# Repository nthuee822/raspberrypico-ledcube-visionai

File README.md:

# raspberrypico-ledcube-visionai
An application of a Raspberry Pi Pico–based 8x8x8 LED cube with Grove Vision AI v2 module

## Introduction

There are many tutorials online about how to build an 8x8x8 LED Cube, but very few showcase practical applications. During an exhibition, we came across the Grove Vision AI V2 module, which inspired us to combine the two into a unique project.

Here’s how our system works: the camera on the Grove Vision AI V2 first recognizes a hand gesture (rock, paper, or scissors). It then sends the result via I²C to the Raspberry Pi Pico 2. The Pico 2 processes the data and communicates with the LED Cube’s PCB through the SPI interface. The PCB, equipped with eight shift registers, controls the LED Cube’s X–Y plane, while an additional perfboard manages the Z-axis. We will present the hardware setup in the next section.

This project is significant for two main reasons. First, we developed a library for the Grove Vision AI V2 to transmit data to Raspberry Pi Pico , making it easier for developers to integrate and leverage its vision features. Second, we created a generalized Raspberry Pi Pico library for the 8x8x8 LED Cube, allowing developers to easily modify display patterns simply by adjusting the code.

## Getting Started

<p align="center"> <br> figure 1. </p>

### Hardware setup: Grove vision AI v2 module

We recommend using the more powerful Grove Vision AI V2 for this project. Setup instructions can be found at the official guide: https://wiki.seeedstudio.com/grove_vision_ai_v2/.

The connection between the Grove Vision AI V2, Raspberry Pi Pico 2, and the PCB with eight shift registers is shown in figure 2.

<p align="center"> <br> figure 2. </p>

### Hardware setup: 8x8x8 LED Cube

The four PCBs, each with eight shift registers, are connected as shown in figure 3.

<p align="center"> <br> figure 3. </p>

The perfboard manages the Z-axis. Pins 6 to 13 on the Raspberry Pi Pico 2 are connected to eight 220 Ω resistors and eight NPN transistors, as shown in figure 4.

<p align="center"> <br> figure 4. </p>

## Software

### Grove vision AI v2 module

We revised the official Seeed_Arduino_SSCMA library (originally for Arduino) into an I²C interface library for the Raspberry Pi Pico.
This makes it easier to integrate the Grove Vision AI V2 with Pico-based projects.

### 8x8x8 LED Cube
We provide two versions of code for the LED Cube:

#### led_cube.c
A standalone project with several predefined special effects.
Simply run the code on the Raspberry Pi Pico, and it will light up the 8x8x8 LED Cube with built-in animations.

#### Cube_general.c
A more generalized implementation.
Developers can easily customize display effects by modifying only the matrix definition.

### Combination
Finally, we integrated everything into a rock–paper–scissors gesture recognition system.
The Grove Vision AI V2 recognizes the gesture, and the result is projected onto the 8x8x8 LED Cube.

For further details, please refer to Cube.cpp.

## Equipment Used

- [Raspberry Pi Pico](https://www.raspberrypi.com/products/raspberry-pi-pico/)
- [Grove Vision AI V2](https://wiki.seeedstudio.com/grove_vision_ai_v2/)
- [Seeed-Arduino_SSCMA Library](https://github.com/Seeed-Studio/Seeed_Arduino_SSCMA/)

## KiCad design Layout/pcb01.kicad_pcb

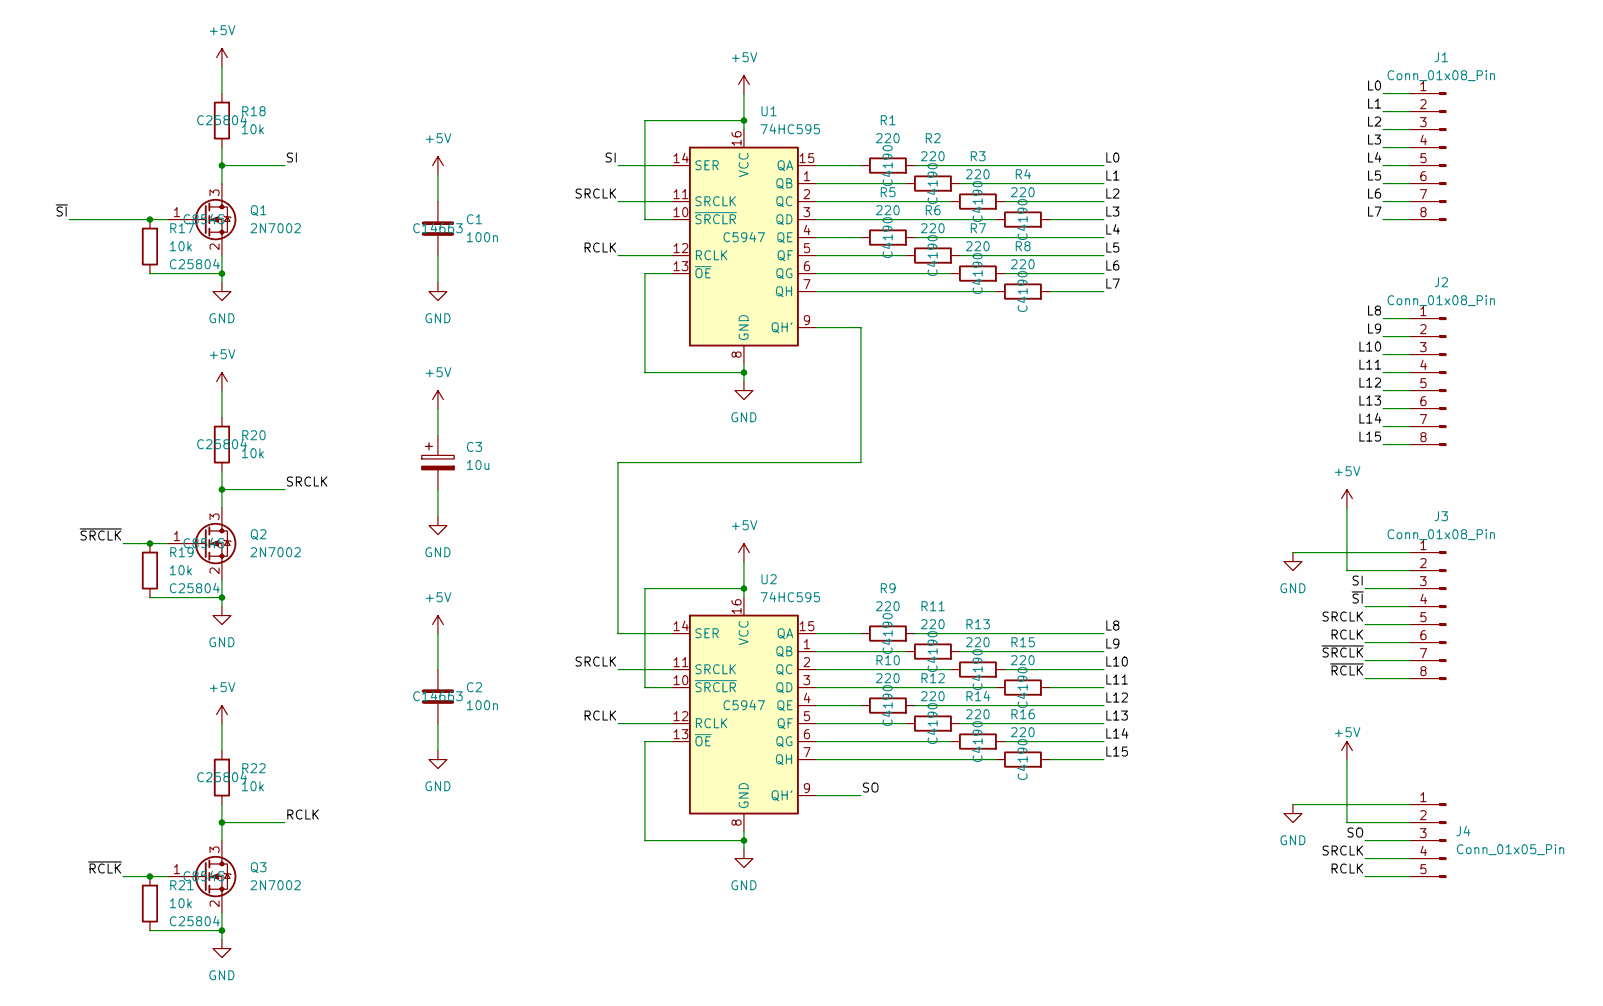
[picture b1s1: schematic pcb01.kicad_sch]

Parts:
C1, C2: 100n; C_0603_1608Metric; LCSC C14663
C3: 10u; C_Radial_D6.3mm_H7.0mm_P2.50mm
J1, J2, J3: Conn_01x08_Pin; PinHeader_1x08_P2.54mm_Vertical
J4: Conn_01x05_Pin; PinHeader_1x05_P2.54mm_Vertical
Q1, Q2, Q3: 2N7002; SOT-23; LCSC C8545
R1, R2, R3, R4, R5, R6, R7, R8, R9, R10, R11, R12, R13, R14, R15, R16: 220; R_0603_1608Metric; LCSC C4190
R17, R18, R19, R20, R21, R22: 10k; R_0603_1608Metric; LCSC C25804
U1, U2: 74HC595; SOIC-16_3.9x9.9mm_P1.27mm; LCSC C5947

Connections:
+5V: C1.1, C2.1, C3.1, J3.2, J4.2, R18.2, R20.2, R22.2, U1.10 (~SRCLR), U1.16 (VCC), U2.10 (~SRCLR), U2.16 (VCC)
/L0: J1.1, R1.2
/L1: J1.2, R2.2
/L2: J1.3, R3.2
/L3: J1.4, R4.2
/L4: J1.5, R5.2
/L5: J1.6, R6.2
/L6: J1.7, R7.2
/L7: J1.8, R8.2
/L8: J2.1, R9.2
/L9: J2.2, R11.2
/L10: J2.3, R13.2
/L11: J2.4, R15.2
/L12: J2.5, R10.2
/L13: J2.6, R12.2
/L14: J2.7, R14.2
/L15: J2.8, R16.2
/RCLK: J3.6, J4.5, Q3.3 (D), R22.1, U1.12 (RCLK), U2.12 (RCLK)
/SI: J3.3, Q1.3 (D), R18.1, U1.14 (SER)
/SO: J4.3, U2.9 (QH')
/SRCLK: J3.5, J4.4, Q2.3 (D), R20.1, U1.11 (SRCLK), U2.11 (SRCLK)
/~RCLK: J3.8, Q3.1 (G), R21.2
/~SI: J3.4, Q1.1 (G), R17.2
/~SRCLK: J3.7, Q2.1 (G), R19.2
GND: C1.2, C2.2, C3.2, J3.1, J4.1, Q1.2 (S), Q2.2 (S), Q3.2 (S), R17.1, R19.1, R21.1, U1.8 (GND), U1.13 (~OE), U2.8 (GND), U2.13 (~OE)
unnamed: R1.1, U1.15 (QA)
unnamed: R2.1, U1.1 (QB)
unnamed: R3.1, U1.2 (QC)
unnamed: R4.1, U1.3 (QD)
unnamed: R5.1, U1.4 (QE)
unnamed: R6.1, U1.5 (QF)
unnamed: R7.1, U1.6 (QG)
unnamed: U1.9 (QH'), U2.14 (SER)
unnamed: R8.1, U1.7 (QH)
unnamed: R9.1, U2.15 (QA)
unnamed: R11.1, U2.1 (QB)
unnamed: R13.1, U2.2 (QC)
unnamed: R15.1, U2.3 (QD)
unnamed: R10.1, U2.4 (QE)
unnamed: R12.1, U2.5 (QF)
unnamed: R14.1, U2.6 (QG)
unnamed: R16.1, U2.7 (QH)

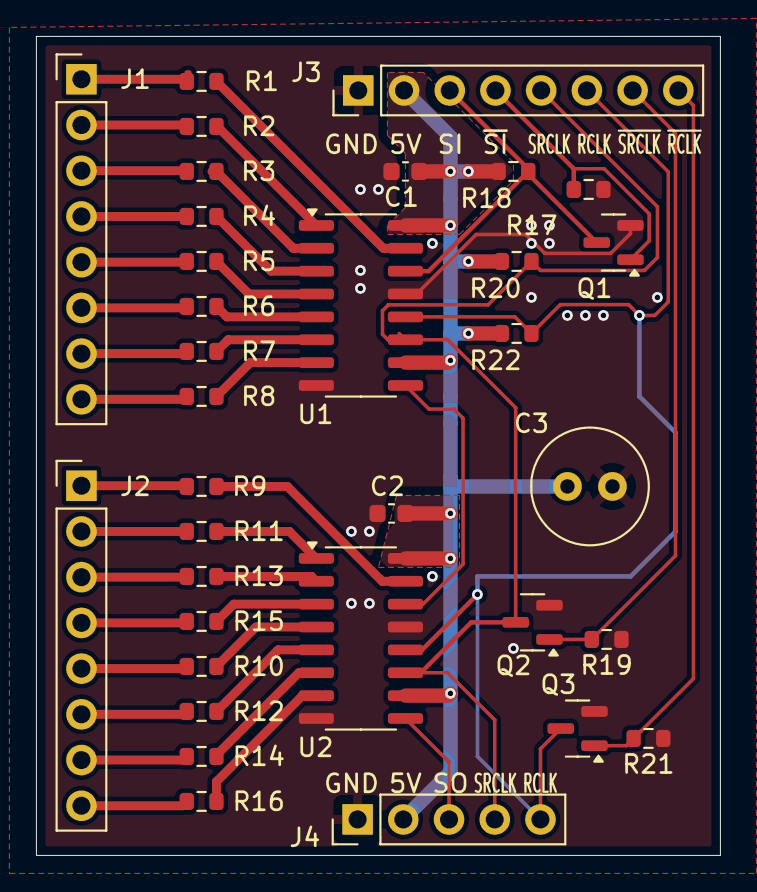
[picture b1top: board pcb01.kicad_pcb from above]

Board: 2 copper layers, 38.0 x 45.5 mm, 34 parts (0 on the bottom side), 42 nets.

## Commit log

2025-09-07 Create Layout
2025-09-07 Create t
